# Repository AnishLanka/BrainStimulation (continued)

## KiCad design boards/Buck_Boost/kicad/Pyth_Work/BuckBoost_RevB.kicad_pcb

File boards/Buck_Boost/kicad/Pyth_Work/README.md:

# BuckBoost Rev B — JLCPCB DFM corrections

Use **BuckBoost_RevB_fabrication.zip** for the next JLCPCB check. Open **BuckBoost_RevB.kicad_pro** in KiCad 10.0 or newer to edit the project. This revision supersedes Rev A for fabrication.

The board retains the TPS63001DRCR 3.3 V converter, original outline and connector locations, and the requested **0.4112 mm design thickness**. The battery operating range supplied was 2.8–3.7 V, with a load above 200 mA. The exact maximum continuous and peak loads remain unspecified.

The later pasted four-channel requirements are assessed in [SYSTEM_REQUIREMENTS_REVIEW.md](SYSTEM_REQUIREMENTS_REVIEW.md). This non-isolated supply has not been validated for the complete four-channel system; its total load and battery power budget remain unknown.

## Corrections in this revision

- Moved C2 and C4 ground vias clear of their component pads and soldermask openings. Rev A's C4 via drill intersected a solder opening, and C2's via was too close.
- Moved four ground vias beside the IC farther from its exposed pad. All 17 ground vias remain tented, and the ground planes remain connected.
- Moved perimeter vias away from printed markings; 14 vias were repositioned in total.
- Removed cramped decorative silkscreen on U1, C1–C4 and R1. Component references remain visible; U1 has a relocated pin-1 marker. Fourteen measured silk-to-pad-mask clearances below 0.15 mm in Rev A are eliminated.
- Increased text to 1.0 mm and minimum silk strokes to 0.16 mm. Repositioned labels to clear pads, holes, other printing and board edges.
- Widened U1 pins 1–10 from 0.24 to **0.25 mm**, retaining 0.60 mm length and 0.50 mm pitch. This is a 0.005 mm extension on each side of TI's nominal land pattern to meet JLCPCB's published minimum SMD-pad dimension. The exposed pad is unchanged.
- Specified ENIG finish in the fabrication metadata. Added stricter local rules: 0.20 mm silk clearance, 1.0 mm text height, 0.15 mm text stroke and 0.09 mm mask-to-unrelated-copper clearance.

## Verification and remaining checker uncertainty

KiCad reports **0 DRC violations, 0 unconnected items, 0 schematic parity issues and 0 ERC violations**. Checks include the configured errors and warnings; no individual DRC exclusions were added. The recovered source circuit, schematic and PCB agree on all **27 component pins across 6 nets**. Outline and terminal pad/drill preservation are checked independently.

`validation/DFM-report.md` and `validation/DFM-geometry.json` contain an independent geometry audit. It checks silk width/height, silk-to-mask, silk-to-drill, via-to-pad/opening, mask webs and mask-to-foreign-net copper. Native SVG/PNG previews are included for visual inspection.

**These are local checks, not a JLCPCB server pass.** The supplied screenshot contained aggregate counts but no feature locations or ZIP identity. Its 14 silk-to-pad findings and six via-to-pad findings are consistent with Rev A geometry. The five orange “solder mask opening exposing trace” findings could not be individually located from that screenshot. No unrelated net is exposed inside a component's mask opening in the local audit. A connecting trace entering its own pad opening is intentional; mask expansion has not been removed just to hide such a warning. Rerun JLCPCB on the Rev B fabrication ZIP and inspect any remaining flagged locations before ordering.

## Circuit and parts

The earlier electrical repair is retained: explicit IC escape traces replace missing copper-pour connections; top and bottom ground planes provide return paths; feedback uses a separate branch to the output capacitor; EN and PS/SYNC remain connected to filtered VINA for always-enabled, forced-PWM operation.

**L1 must be Coilcraft XFL4020-222MEC, 2.2 uH**, using the supplied footprint. The original library metadata conflicted with the displayed value and described an unsuitable 10 uH, 500 mA part. Do not substitute the original L1 part. C1–C3 are Murata GRM21BR61E106KA73L, 10 uF/25 V/X5R; C4 is TDK C2012X7R2A104K125AA, 100 nF/100 V/X7R; R1 is Vishay CRCW0402100RFKED, 100 ohm. See BOM.csv for complete purchasing details.

J1 is input; J2 is output. **Pin 1 is positive and pin 2 is GND on both connectors.** Source references IN/OUT were renamed J1/J2. Connector positions, 5 mm pitch and 1.50 mm drills are preserved. U1's exposed pad uses four paste windows, approximately 61% area coverage; review the stencil process with the assembler.

## Manufacturing settings

| Item | Specification |
|---|---|
| Outline at Edge.Cuts centerline | 58.928 × 17.018 mm |
| Copper layers | 2 |
| Design thickness | 0.4112 mm, preserved |
| Source stackup | 0.32 mm FR-4 core, 0.0356 mm copper per side, 0.01 mm mask per side |
| Copper weight | Approximately 1 oz per side |
| Finish | ENIG |
| Via diameter / drill | 0.60 / 0.30 mm; tented both sides |
| Holes | 17 vias and 4 terminal holes, all plated |
| Copper clearance / copper to edge | 0.20 / 0.50 mm |
| Mask expansion | 0.0508 mm on U1; other pad overrides preserved |
| Minimum U1 mask web | Approximately 0.1484 mm |
| Coordinate origin | Lower-left outline corner, shared by Gerbers, drills and placement |

JLCPCB lists 0.4 mm as its nominal thin-board option and ±0.1 mm thickness tolerance below 1 mm. The editable design remains 0.4112 mm; do not substitute a thicker board. Confirm the supplied stackup/tolerance meets the product fit. ENIG is specified because JLCPCB does not support HASL on boards at or below 0.4 mm. The thin board and heavy terminal blocks need appropriate mechanical support.

Use the complete Rev B fabrication set together. Do not mix it with previous exports. The empty NPTH file is intentional. The fabrication ZIP contains manufacturing layers, job metadata and drill files; drill maps are in the full project under fabrication/. No filled or plated-over via-in-pad process is requested. BOM and placement are generic assembly data; assembly-service-specific ordering codes, rotations and panel requirements still require the assembler's review.

## Prototype validation

This revision has not been physically tested. Inspect polarity, solder bridges, exposed-pad soldering and L1 before applying power. Check for input/output shorts, then use a current-limited bench supply and a controlled dummy load. Confirm 3.3 V at no load and above 200 mA; 250 mA is a starting test point, not a guaranteed maximum rating. Sweep input from 3.7 to 2.8 V, including startup at both ends, and measure regulation, ripple and temperature. Repeat with the actual system's continuous and pulsed load before connecting it.

The complete system must provide suitable battery protection/cutoff. No physical load, thermal, EMI or system-level safety validation was performed. Prior measurements on the old board do not validate this revision.

## Contents and references

- Editable PCB/schematic/project, portable local symbol/footprint libraries.
- BOM.csv, placement.csv, fabrication layers and native previews.
- validation/: electrical checks, source comparison, independent DFM measurements and via-move record.
- SHA256SUMS.txt: file-integrity hashes.

References checked for this revision: [JLCPCB fabrication capabilities](https://jlcpcb.com/capabilities/pcb-), [TI TPS63001 datasheet](https://www.ti.com/lit/ds/symlink/tps63001.pdf), [TI evaluation module](https://www.ti.com/lit/ug/slvu156/slvu156.pdf), [Coilcraft XFL4020](https://www.coilcraft.com/getmedia/50632d43-da1b-4cdb-8ab4-3029cab51df3/xfl4020.pdf). Component-specific links are included in BOM.csv.

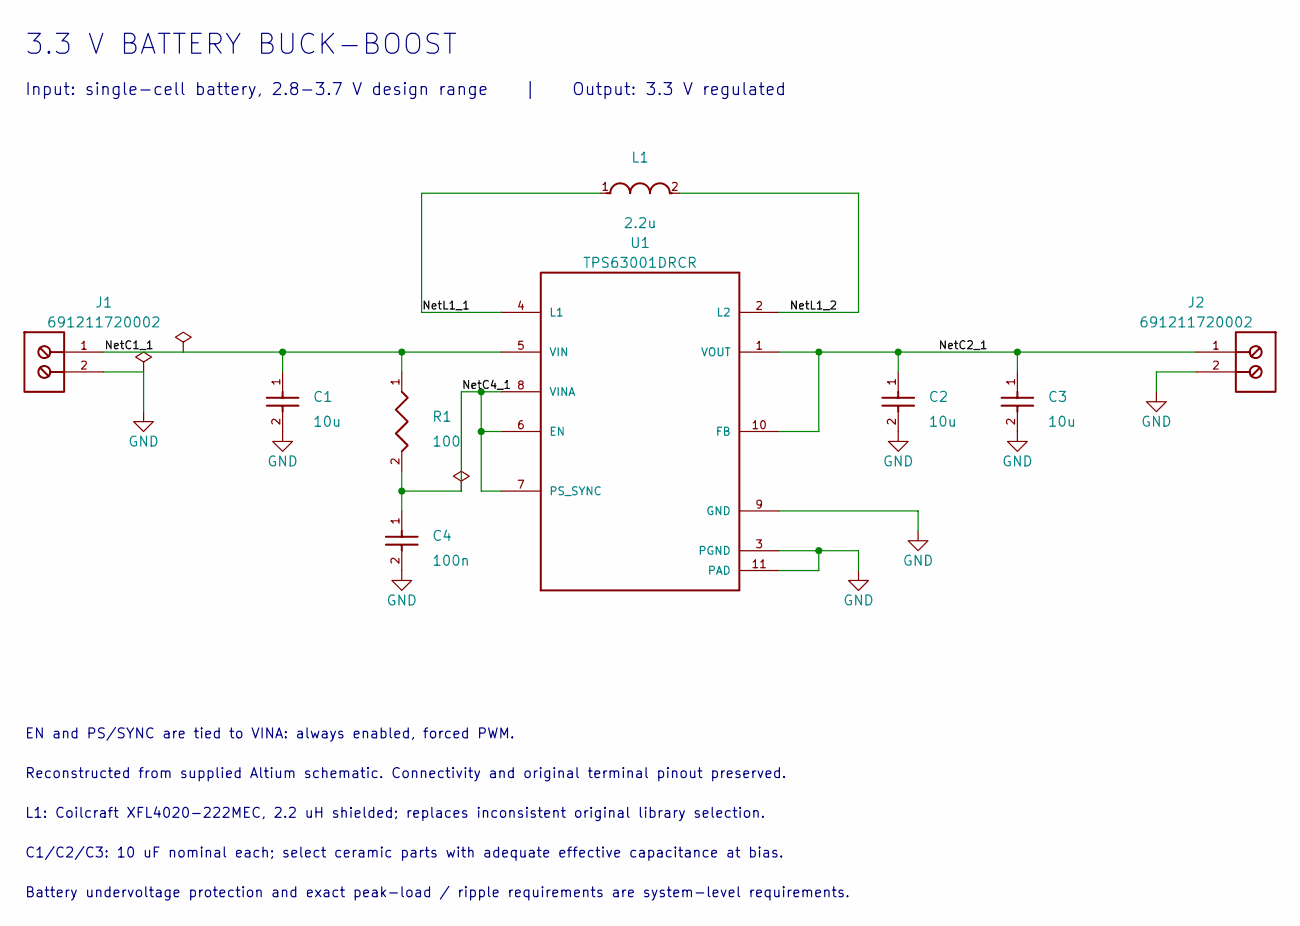
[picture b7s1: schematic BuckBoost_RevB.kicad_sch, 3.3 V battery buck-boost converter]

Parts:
C1, C2, C3: 10u; C1_0805; MPN GRM21BR61E106KA73L
C4: 100n; C4_0805; MPN C2012X7R2A104K125AA
J1: 691211720002; IN_691211720002; MPN 691211720002
J2: 691211720002; OUT_691211720002; MPN 691211720002
L1: 2.2u; L1_2u2; MPN XFL4020-222MEC
R1: 100; R1_0402; MPN CRCW0402100RFKED
U1: TPS63001DRCR; U1_TPS63001; MPN TPS63001DRCR

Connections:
/NetC1_1: C1.1, J1.1, R1.1, U1.5 (VIN)
/NetC2_1: C2.1, C3.1, J2.1, U1.1 (VOUT), U1.10 (FB)
/NetC4_1: C4.1, R1.2, U1.6 (EN), U1.7 (PS_SYNC), U1.8 (VINA)
/NetL1_1: L1.1, U1.4 (L1)
/NetL1_2: L1.2, U1.2 (L2)
GND: C1.2, C2.2, C3.2, C4.2, J1.2, J2.2, U1.3 (PGND), U1.9 (GND), U1.11 (PAD)

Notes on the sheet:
3.3 V BATTERY BUCK-BOOST
Input: single-cell battery, 2.8-3.7 V design range | Output: 3.3 V regulated
EN and PS/SYNC are tied to VINA: always enabled, forced PWM.
Reconstructed from supplied Altium schematic. Connectivity and original terminal pinout preserved.
L1: Coilcraft XFL4020-222MEC, 2.2 uH shielded; replaces inconsistent original library selection.
C1/C2/C3: 10 uF nominal each; select ceramic parts with adequate effective capacitance at bias.
Battery undervoltage protection and exact peak-load / ripple requirements are system-level requirements.

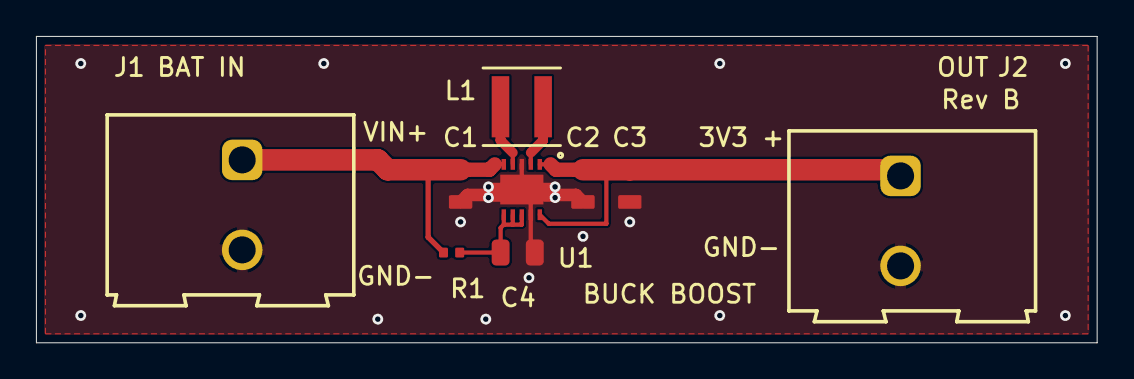
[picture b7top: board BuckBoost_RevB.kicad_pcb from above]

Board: 2 copper layers, 58.9 x 17.0 mm, 9 parts (0 on the bottom side), 6 nets.

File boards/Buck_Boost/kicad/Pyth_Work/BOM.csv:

Reference,Quantity,Value,Manufacturer,MPN,Footprint,Specification,Datasheet
C1,1,10u,Murata,GRM21BR61E106KA73L,BuckBoostLocal:C1_0805,10 uF +/-10%; X5R; 25 V; 0805; verify effective capacitance at operating bias,https://search.murata.co.jp/Ceramy/image/img/A01X/G101/ENG/G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
C2,1,10u,Murata,GRM21BR61E106KA73L,BuckBoostLocal:C1_0805,10 uF +/-10%; X5R; 25 V; 0805; verify effective capacitance at operating bias,https://search.murata.co.jp/Ceramy/image/img/A01X/G101/ENG/G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
C3,1,10u,Murata,GRM21BR61E106KA73L,BuckBoostLocal:C1_0805,10 uF +/-10%; X5R; 25 V; 0805; verify effective capacitance at operating bias,https://search.murata.co.jp/Ceramy/image/img/A01X/G101/ENG/G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
C4,1,100n,TDK,C2012X7R2A104K125AA,BuckBoostLocal:C4_0805,100 nF +/-10%; X7R; 100 V; 0805; increased voltage rating from source50 V,https://product.tdk.com/en/search/capacitor/ceramic/mlcc/inf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
J1,1,691211720002,Wurth Elektronik,691211720002,BuckBoostLocal:IN_691211720002,"Source terminal block retained; 2 positions; 5 mm pitch; pin1 positive, pin2 GND",
J2,1,691211720002,Wurth Elektronik,691211720002,BuckBoostLocal:OUT_691211720002,"Source terminal block retained; 2 positions; 5 mm pitch; pin1 positive, pin2 GND",
L1,1,2.2u,Coilcraft,XFL4020-222MEC,BuckBoostLocal:L1_2u2,2.2 uH +/-20%; shielded; DCR 23.5 mOhm max; Isat 3.1 A at 10% loss,https://www.coilcraft.com/getmedia/50632d43-da1b-4cdb-8ab4-3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
R1,1,100,Vishay,CRCW0402100RFKED,BuckBoostLocal:R1_0402,100 ohm +/-1%; 0402; 63 mW standard operation,https://www.vishay.com/docs/20035/dcrcwe3.pdf
U1,1,TPS63001DRCR,Texas Instruments,TPS63001DRCR,BuckBoostLocal:U1_TPS63001,Fixed 3.3 V buck-boost regulator; VSON-10 exposed pad,https://www.ti.com/lit/ds/symlink/tps63001.pdf

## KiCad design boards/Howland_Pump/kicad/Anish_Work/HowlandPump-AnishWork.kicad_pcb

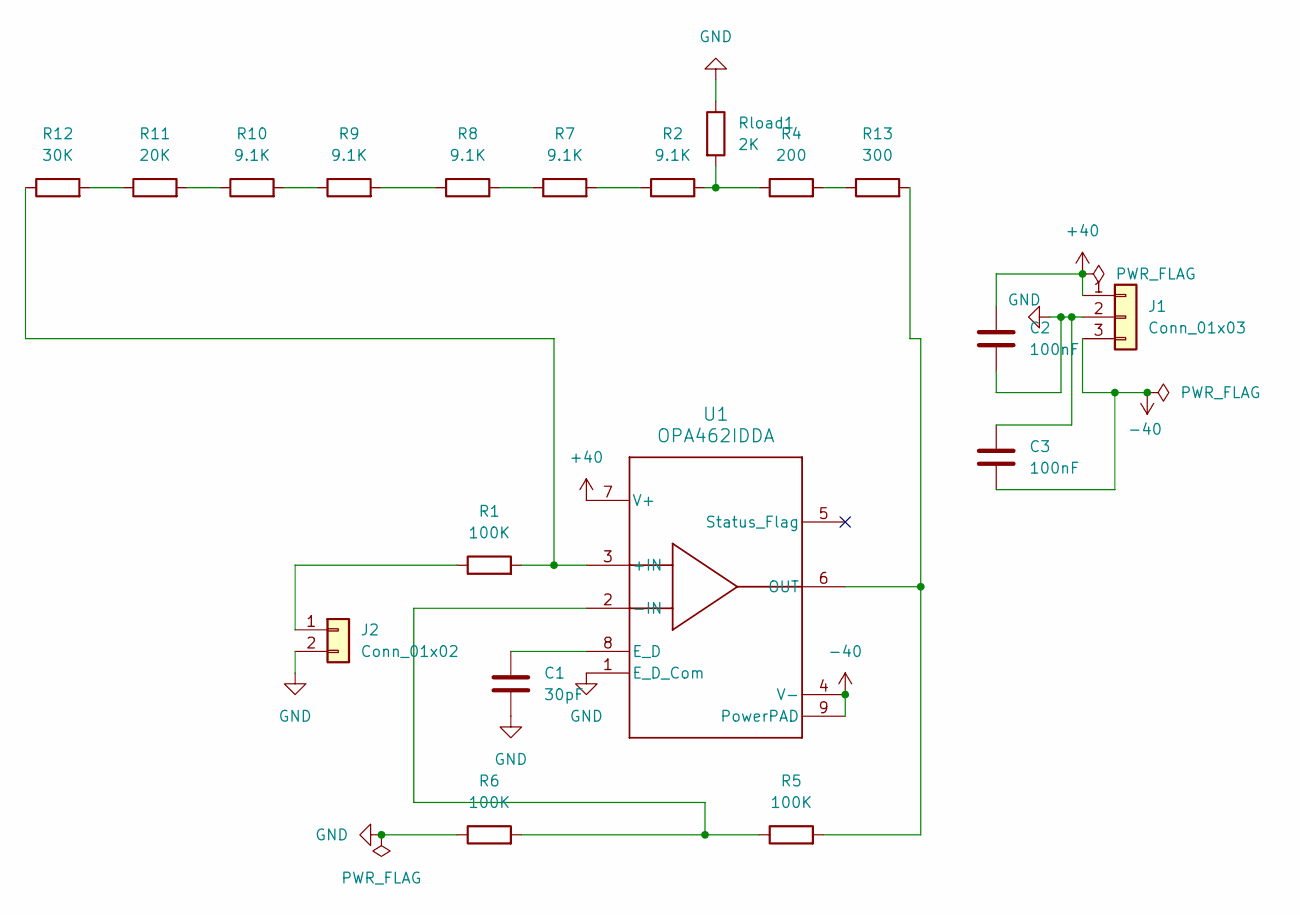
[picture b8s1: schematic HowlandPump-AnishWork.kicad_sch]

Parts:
C1: 30pF; C_1206_3216Metric
C2, C3: 100nF; C_1206_3216Metric
J1: Conn_01x03; PinHeader_1x03_P2.54mm_Vertical
J2: Conn_01x02; PinHeader_1x02_P2.54mm_Vertical
R1, R5, R6: 100K; R_1206_3216Metric
R2, R7, R8, R9, R10: 9.1K; R_1206_3216Metric
R4: 200; R_1206_3216Metric
R11: 20K; R_1206_3216Metric
R12: 30K; R_1206_3216Metric
R13: 300; R_1206_3216Metric
Rload1: 2K; R_1206_3216Metric
U1: OPA462IDDA; DDA0008J-IPC_A

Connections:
+40: C2.1, J1.1, U1.7 (V+)
-40: C3.2, J1.3, U1.4 (V-), U1.9 (PowerPAD)
GND: C1.2, C2.2, C3.1, J1.2, J2.2, R6.1, Rload1.1, U1.1 (E_D_Com)
unnamed: J2.1, R1.1
unnamed: R2.1, R7.2
unnamed: R2.2, R4.1, Rload1.2
unnamed: R7.1, R8.2
unnamed: R8.1, R9.2
unnamed: R10.1, R11.2
unnamed: R9.1, R10.2
unnamed: R11.1, R12.2
unnamed: R4.2, R13.1
unnamed: R1.2, R12.1, U1.3 (+IN)
unnamed: R5.1, R6.2, U1.2 (-IN)
unnamed: C1.1, U1.8 (E_D)
unnamed: R5.2, R13.2, U1.6 (OUT)

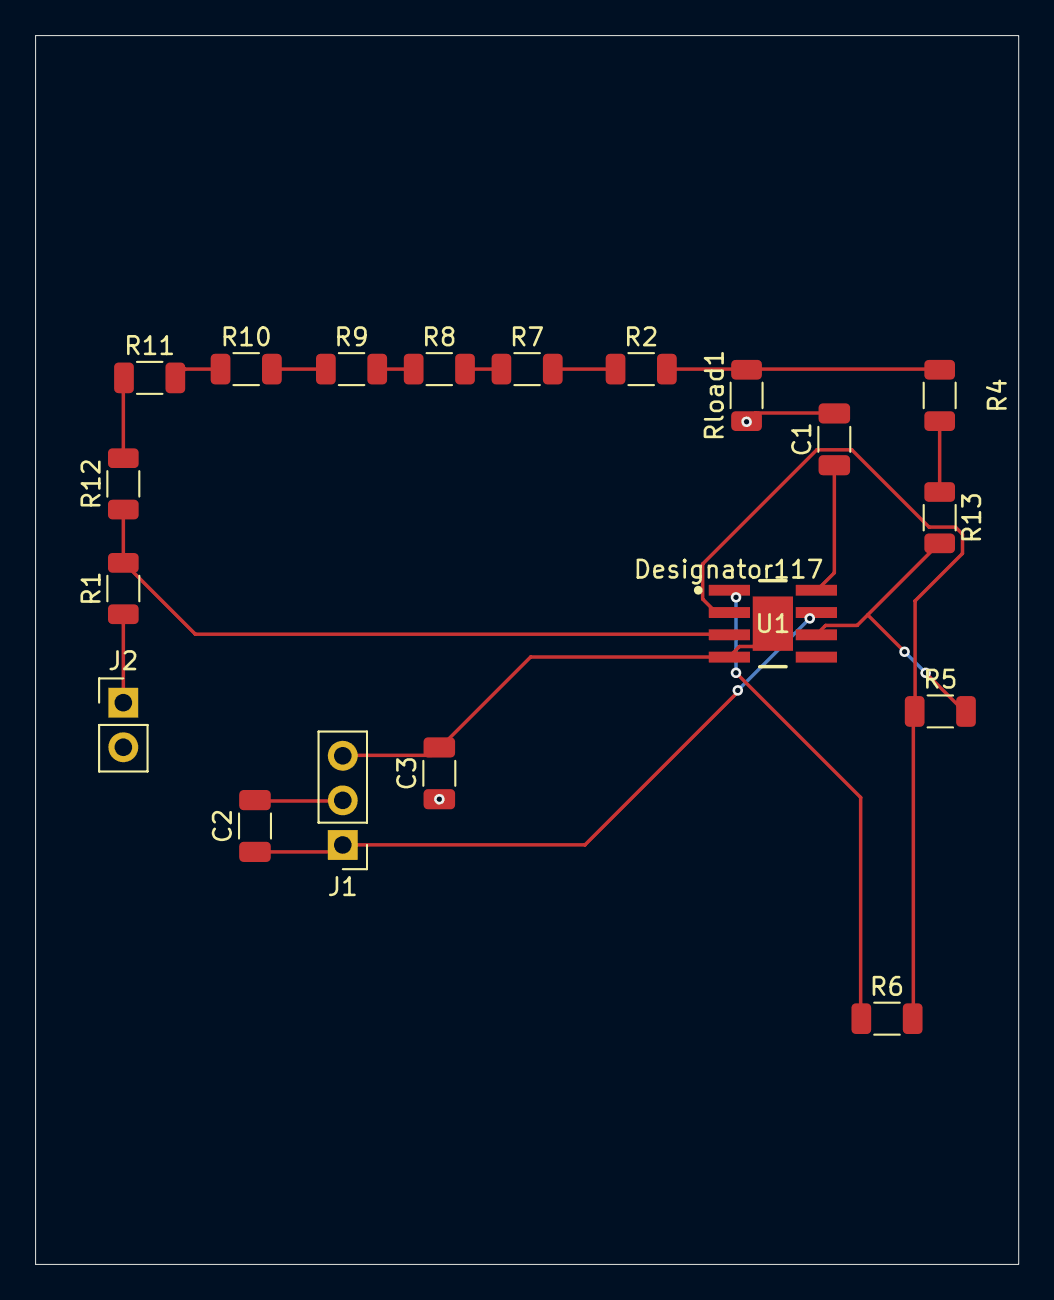
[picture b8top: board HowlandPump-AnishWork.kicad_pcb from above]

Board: 2 copper layers, 56.0 x 70.0 mm, 19 parts (0 on the bottom side), 16 nets.
